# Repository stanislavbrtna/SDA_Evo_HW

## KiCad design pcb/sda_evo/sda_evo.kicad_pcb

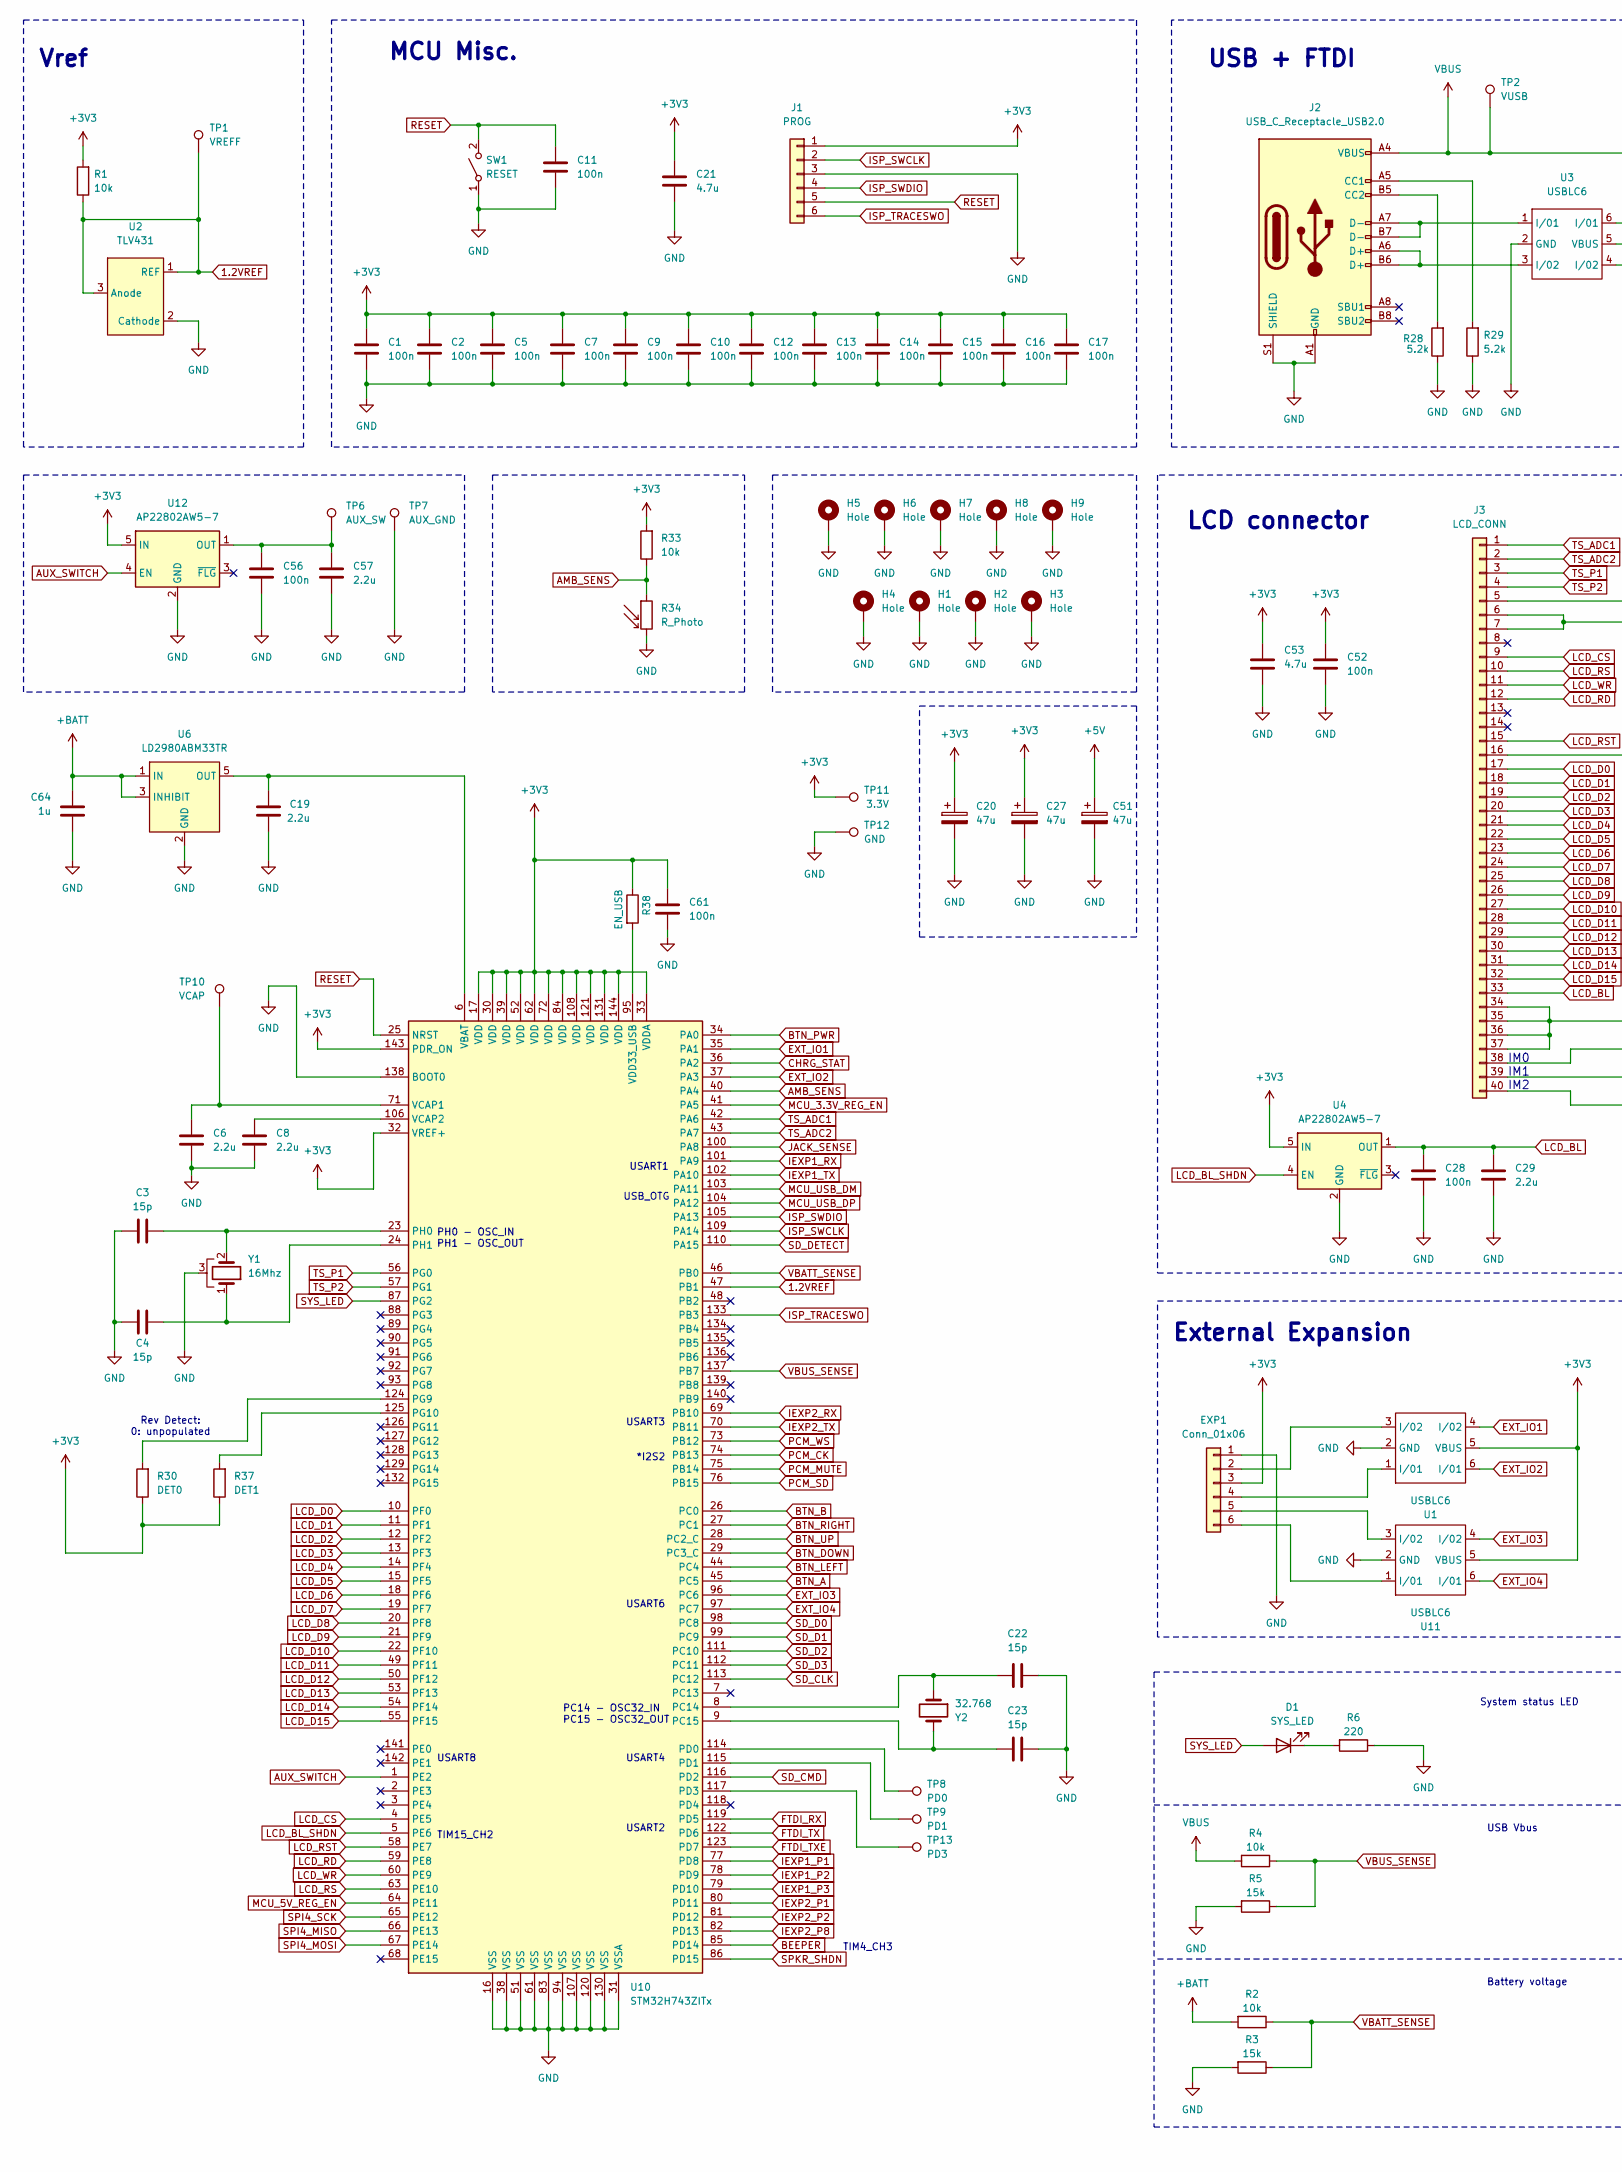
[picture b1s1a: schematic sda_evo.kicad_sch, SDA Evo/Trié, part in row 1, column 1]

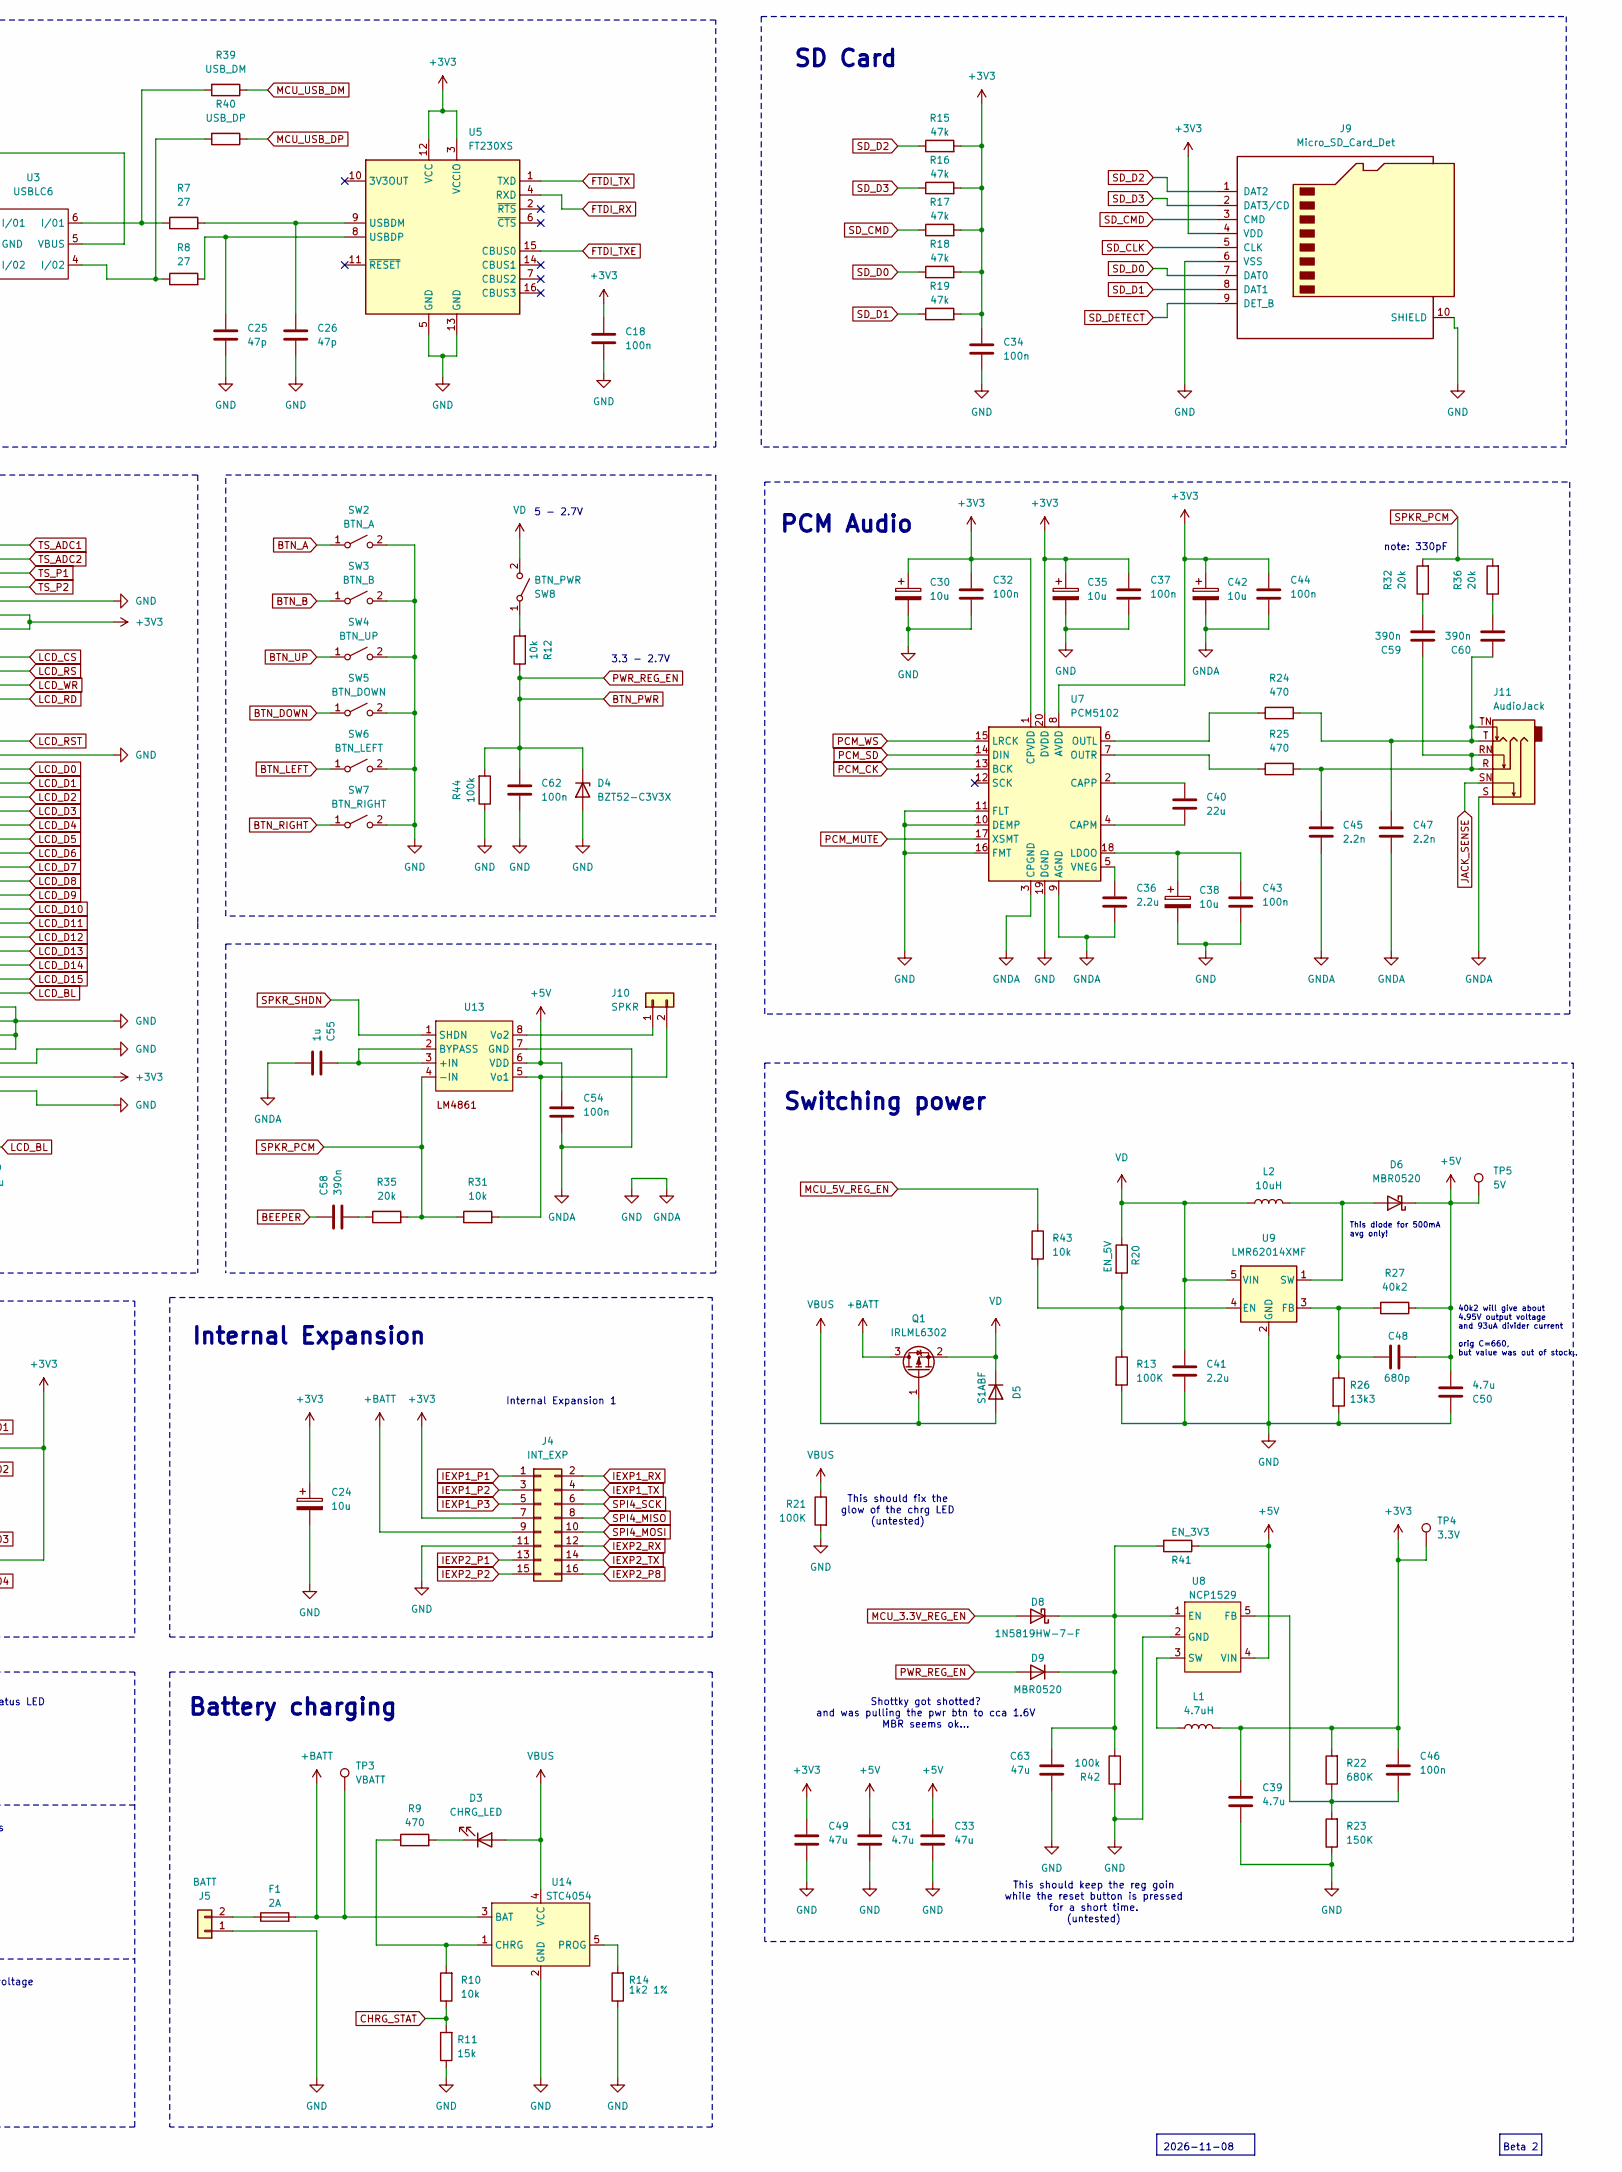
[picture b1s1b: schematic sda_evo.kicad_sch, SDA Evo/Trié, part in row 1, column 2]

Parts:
C1, C2, C5, C7, C9, C10, C11, C12, C13, C14, C15, C16, C17, C18, C28, C32, C34, C37, C43, C44, C46, C52, C54, C56, C61, C62: 100n; C_0805_2012Metric_Pad1.18x1.45mm_HandSolder
C3, C4, C22, C23: 15p; C_0805_2012Metric_Pad1.18x1.45mm_HandSolder
C6, C8, C19, C29, C36, C41, C57: 2.2u; C_0805_2012Metric_Pad1.18x1.45mm_HandSolder
C20, C27, C51: 47u; CP_EIA-7343-15_Kemet-W_Pad2.25x2.55mm_HandSolder
C21, C31, C39, C50, C53: 4.7u; C_0805_2012Metric_Pad1.18x1.45mm_HandSolder
C24, C30, C35, C38, C42: 10u; C_0805_2012Metric_Pad1.18x1.45mm_HandSolder
C25, C26: 47p; C_0805_2012Metric_Pad1.18x1.45mm_HandSolder
C33, C49, C63: 47u; C_0805_2012Metric_Pad1.18x1.45mm_HandSolder
C40: 22u; C_0805_2012Metric_Pad1.18x1.45mm_HandSolder
C45, C47: 2.2n; C_0805_2012Metric_Pad1.18x1.45mm_HandSolder
C48: 680p; C_0805_2012Metric_Pad1.18x1.45mm_HandSolder
C55, C64: 1u; C_0805_2012Metric_Pad1.18x1.45mm_HandSolder
C58, C59, C60: 390n; C_0805_2012Metric_Pad1.18x1.45mm_HandSolder
D1: SYS_LED; LED_D3.0mm_FlatTop
D3: CHRG_LED; LED_SMD_custom
D4: BZT52-C3V3X; Nexperia_CFP3_SOD-123W
D5: S1ABF; D_SMB
D6, D9: MBR0520; D_SOD-123
D8: 1N5819HW-7-F; D_SOD-123
EXP1: Conn_01x06; 2.54x6_flat
F1: 2A; Fuse_1206_3216Metric
H1, H2, H3, H4, H5, H6, H7, H8, H9: Hole; Hole 1,6mm
J1: PROG; PinHeader_1x06_P1.27mm_Vertical
J2: USB_C_Receptacle_USB2.0; USB_C
J3: LCD_CONN; Hirose_FH12-40S-0.5SH_1x40-1MP_P0.50mm_Horizontal
J4: INT_EXP; PinHeader_2x08_P1.27mm_Vertical_SMD
J5: BATT; PinHeader_1x02_P2.54mm_Horizontal
J9: Micro_SD_Card_Det; SD-Connector
J10: SPKR; PinHeader_1x02_P1.27mm_Vertical
J11: AudioJack; 3.5 Jack
L1: 4.7uH; HCM1A4020V2
L2: 10uH; SDN0530MT100
Q1: IRLML6302; SOT-23
R1, R2, R4, R10, R12, R31, R33, R43: 10k; R_0805_2012Metric_Pad1.20x1.40mm_HandSolder
R3, R5, R11: 15k; R_0805_2012Metric_Pad1.20x1.40mm_HandSolder
R6: 220; R_0805_2012Metric_Pad1.20x1.40mm_HandSolder
R7, R8: 27; R_0805_2012Metric_Pad1.20x1.40mm_HandSolder
R9, R24, R25: 470; R_0805_2012Metric_Pad1.20x1.40mm_HandSolder
R13, R21: 100K; R_0805_2012Metric_Pad1.20x1.40mm_HandSolder
R14: 1k2 1%; R_0805_2012Metric_Pad1.20x1.40mm_HandSolder
R15, R16, R17, R18, R19: 47k; R_0805_2012Metric_Pad1.20x1.40mm_HandSolder
R20: EN_5V; SolderJumper-2_P1.3mm_Open_TrianglePad1.0x1.5mm
R22: 680K; R_0805_2012Metric_Pad1.20x1.40mm_HandSolder
R23: 150K; R_0805_2012Metric_Pad1.20x1.40mm_HandSolder
R26: 13k3; R_0805_2012Metric_Pad1.20x1.40mm_HandSolder
R27: 40k2; R_0805_2012Metric_Pad1.20x1.40mm_HandSolder
R28, R29: 5.2k; R_0805_2012Metric_Pad1.20x1.40mm_HandSolder
R30: DET0; SolderJumper-2_P1.3mm_Open_TrianglePad1.0x1.5mm
R32, R35, R36: 20k; R_0805_2012Metric_Pad1.20x1.40mm_HandSolder
R34: R_Photo; LED_D5.0mm
R37: DET1; SolderJumper-2_P1.3mm_Open_TrianglePad1.0x1.5mm
R38: EN_USB; SolderJumper-2_P1.3mm_Open_TrianglePad1.0x1.5mm
R39: USB_DM; SolderJumper-2_P1.3mm_Open_TrianglePad1.0x1.5mm
R40: USB_DP; SolderJumper-2_P1.3mm_Open_TrianglePad1.0x1.5mm
R41: EN_3V3; SolderJumper-2_P1.3mm_Open_TrianglePad1.0x1.5mm
R42, R44: 100k; R_0805_2012Metric_Pad1.20x1.40mm_HandSolder
SW1: RESET; SW_SPST_RESET
SW2: BTN_A; SW_SPST_PTS645
SW3: BTN_B; SW_SPST_PTS645
SW4: BTN_UP; SW_SPST_PTS645
SW5: BTN_DOWN; SW_SPST_PTS645
SW6: BTN_LEFT; SW_SPST_PTS645
SW7: BTN_RIGHT; SW_SPST_PTS645
SW8: BTN_PWR; SW_Push_1P1T_NO_CK_KMR2_PWR
TP1: VREFF; TestPoint_Pad_D1.0mm
TP2: VUSB; TestPoint_Pad_D1.0mm
TP3: VBATT; TestPoint_Pad_D1.0mm
TP4: 3.3V; TestPoint_Pad_D1.0mm
TP5: 5V; TestPoint_Pad_D1.0mm
TP6: AUX_SW; TestPoint_Pad_D2.5mm
TP7: AUX_GND; TestPoint_Pad_D2.5mm
TP8: PD0; TestPoint_Pad_D2.5mm
TP9: PD1; TestPoint_Pad_D2.5mm
TP10: VCAP; TestPoint_Pad_D1.0mm
TP11: 3.3V; TestPoint_Pad_D2.5mm
TP12: GND; TestPoint_Pad_D2.5mm
TP13: PD3; TestPoint_Pad_D2.5mm
U1, U3, U11: USBLC6; SOT-23-6_Handsoldering
U2: TLV431; TSOT-23
U4, U12: AP22802AW5-7; SOT-23-5_HandSoldering
U5: FT230XS; SSOP-16_3.9x4.9mm_P0.635mm
U6: LD2980ABM33TR; SOT-23-5_HandSoldering
U7: PCM5102; TSSOP-20_4.4x6.5mm_P0.65mm
U8: NCP1529; SOT-23-5_HandSoldering
U9: LMR62014XMF; SOT-23-5_HandSoldering
U10: STM32H743ZITx; LQFP-144_20x20mm_P0.5mm
U13: LM4861; HSOP-8-1EP_3.9x4.9mm_P1.27mm_EP2.41x3.1mm
U14: STC4054; SOT-23-5_HandSoldering
Y1: 16Mhz; SMDXT224
Y2: 32.768; Crystal_SMD_6.7x1.5mm_HandSoldering

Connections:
1.2VREF: R1.1, TP1.1, U2.1 (REF), U2.3 (Anode), U10.47 (PB1)
+3V3: C1.1, C2.1, C5.1, C7.1, C9.1, C10.1, C12.1, C13.1, C14.1, C15.1, C16.1, C17.1, C18.1, C20.1, C21.1, C24.1, C27.1, C30.1, C32.1, C34.1, C35.1, C37.1, C39.1, C42.1, C44.1, C46.1, C49.1, C52.1, C53.1, C61.1, EXP1.3, J1.1, J3.6, J3.7, J3.39, J4.7, J9.4 (VDD), L1.2, R1.2, R15.2, R16.2, R17.2, R18.2, R19.2, R22.2, R30.1, R33.2, R37.1, R38.1, TP4.1, TP11.1, U1.5 (VBUS), U4.5 (IN), U5.3 (VCCIO), U5.12 (VCC), U7.1 (CPVDD), U7.8 (AVDD), U7.20 (DVDD), U10.17 (VDD), U10.30 (VDD), U10.32 (VREF+), U10.33 (VDDA), U10.39 (VDD), U10.52 (VDD), U10.62 (VDD), U10.72 (VDD), U10.84 (VDD), U10.108 (VDD), U10.121 (VDD), U10.131 (VDD), U10.143 (PDR_ON), U10.144 (VDD), U11.5 (VBUS), U12.5 (IN)
+5V: C31.1, C33.1, C48.2, C50.1, C51.1, C54.1, D6.1 (K), R27.1, R41.1, TP5.1, U8.4 (VIN), U13.6 (VDD)
+BATT: C64.1, F1.2, J4.9, Q1.3 (D), R2.2, TP3.1, U6.1 (IN), U6.3 (INHIBIT), U14.3 (BAT)
AMB_SENS: R33.1, R34.1, U10.40 (PA4)
AUX_SWITCH: U10.1 (PE2), U12.4 (EN)
BEEPER: C58.1, U10.85 (PD14)
BTN_A: SW2.1 (A), U10.45 (PC5)
BTN_B: SW3.1 (A), U10.26 (PC0)
BTN_DOWN: SW5.1 (A), U10.29 (PC3_C)
BTN_LEFT: SW6.1 (A), U10.44 (PC4)
BTN_PWR: C62.1, D4.1 (K), D9.2 (A), R12.1, R44.2, U10.34 (PA0)
BTN_RIGHT: SW7.1 (A), U10.27 (PC1)
BTN_UP: SW4.1 (A), U10.28 (PC2_C)
CHRG_STAT: R10.1, R11.2, U10.36 (PA2)
EXT_IO1: U1.4 (I/02), U10.35 (PA1)
EXT_IO2: U1.6 (I/01), U10.37 (PA3)
EXT_IO3: U10.96 (PC6), U11.4 (I/02)
EXT_IO4: U10.97 (PC7), U11.6 (I/01)
FTDI_RX: U5.4 (RXD), U10.119 (PD5)
FTDI_TX: U5.1 (TXD), U10.122 (PD6)
FTDI_TXE: U5.15 (CBUS0), U10.123 (PD7)
GND: C1.2, C2.2, C3.1, C4.1, C5.2, C6.2, C7.2, C8.2, C9.2, C10.2, C11.2, C12.2, C13.2, C14.2, C15.2, C16.2, C17.2, C18.2, C19.2, C20.2, C21.2, C22.1, C23.1, C24.2, C25.2, C26.2, C27.2, C28.2, C29.2, C30.2, C31.2, C32.2, C33.2, C34.2, C35.2, C36.2, C37.2, C38.2, C39.2, C41.2, C42.2, C43.2, C44.2, C45.2, C47.2, C49.2, C50.2, C51.2, C52.2, C53.2, C54.2, C55.2, C56.2, C57.2, C61.2, C62.2, C63.2, C64.2, D4.2 (A), EXP1.1, H1.1, H2.1, H3.1, H4.1, H5.1, H6.1, H7.1, H8.1, H9.1, J1.3, J2.A1 (GND), J2.A12 (GND), J2.B1 (GND), J2.B12 (GND), J2.S1 (SHIELD), J3.5, J3.16, J3.34, J3.35, J3.36, J3.37, J3.38, J3.40, J4.11, J5.1, J9.6 (VSS), J9.10 (SHIELD), J11.S, R3.2, R5.2, R6.1, R11.1, R13.2, R14.1, R21.2, R23.1, R26.2, R28.1, R29.1, R34.2, R42.2, R44.1, SW1.1 (A), SW2.2 (B), SW3.2 (B), SW4.2 (B), SW5.2 (B), SW6.2 (B), SW7.2 (B), TP7.1, TP12.1, U1.2 (GND), U2.2 (Cathode), U3.2 (GND), U4.2 (GND), U5.5 (GND), U5.13 (GND), U6.2 (GND), U7.3 (CPGND), U7.9 (AGND), U7.10 (DEMP), U7.11 (FLT), U7.16 (FMT), U7.19 (DGND), U8.2 (GND), U9.2 (GND), U10.16 (VSS), U10.31 (VSSA), U10.38 (VSS), U10.51 (VSS), U10.61 (VSS), U10.83 (VSS), U10.94 (VSS), U10.107 (VSS), U10.120 (VSS), U10.130 (VSS), U10.138 (BOOT0), U11.2 (GND), U12.2 (GND), U13.7 (GND), U14.2 (GND), Y1.3
IEXP1_P1: J4.1, U10.77 (PD8)
IEXP1_P2: J4.3, U10.78 (PD9)
IEXP1_P3: J4.5, U10.79 (PD10)
IEXP1_RX: J4.2, U10.101 (PA9)
IEXP1_TX: J4.4, U10.102 (PA10)
IEXP2_P1: J4.13, U10.80 (PD11)
IEXP2_P2: J4.15, U10.81 (PD12)
IEXP2_P8: J4.16, U10.82 (PD13)
IEXP2_RX: J4.12, U10.69 (PB10)
IEXP2_TX: J4.14, U10.70 (PB11)
ISP_SWCLK: J1.2, U10.109 (PA14)
ISP_SWDIO: J1.4, U10.105 (PA13)
ISP_TRACESWO: J1.6, U10.133 (PB3)
JACK_SENSE: J11.SN, U10.100 (PA8)
LCD_BL: C28.1, C29.1, J3.33, U4.1 (OUT)
LCD_BL_SHDN: U4.4 (EN), U10.5 (PE6)
LCD_CS: J3.9, U10.4 (PE5)
LCD_D0: J3.17, U10.10 (PF0)
LCD_D1: J3.18, U10.11 (PF1)
LCD_D2: J3.19, U10.12 (PF2)
LCD_D3: J3.20, U10.13 (PF3)
LCD_D4: J3.21, U10.14 (PF4)
LCD_D5: J3.22, U10.15 (PF5)
LCD_D6: J3.23, U10.18 (PF6)
LCD_D7: J3.24, U10.19 (PF7)
LCD_D8: J3.25, U10.20 (PF8)
LCD_D9: J3.26, U10.21 (PF9)
LCD_D10: J3.27, U10.22 (PF10)
LCD_D11: J3.28, U10.49 (PF11)
LCD_D12: J3.29, U10.50 (PF12)
LCD_D13: J3.30, U10.53 (PF13)
LCD_D14: J3.31, U10.54 (PF14)
LCD_D15: J3.32, U10.55 (PF15)
LCD_RD: J3.12, U10.59 (PE8)
LCD_RS: J3.10, U10.63 (PE10)
LCD_RST: J3.15, U10.58 (PE7)
LCD_WR: J3.11, U10.60 (PE9)
MCU_3.3V_REG_EN: D8.2 (A), U10.41 (PA5)
MCU_5V_REG_EN: R43.1, U10.64 (PE11)
MCU_USB_DM: R39.1, U10.103 (PA11)
MCU_USB_DP: R40.1, U10.104 (PA12)
unnamed: C45.1, C59.1, J11.R, J11.RN, R25.2
unnamed: C47.1, C60.1, J11.T, J11.TN, R24.2
unnamed: C58.2, R35.1
unnamed: C59.2, R32.1
unnamed: C60.2, R36.1
unnamed: D1.1 (K), R6.2
unnamed: D3.1 (K), R9.2
unnamed: D6.2 (A), L2.2, U9.1 (SW)
unnamed: C63.1, D8.1 (K), D9.1 (K), R41.2, R42.1, U8.1 (EN)
unnamed: EXP1.2, U1.3 (I/02)
unnamed: EXP1.4, U1.1 (I/01)
unnamed: EXP1.5, U11.3 (I/02)
unnamed: EXP1.6, U11.1 (I/01)
unnamed: J2.A5 (CC1), R29.2
unnamed: J2.B5 (CC2), R28.2
unnamed: J2.A6 (D+), J2.B6 (D+), U3.3 (I/02)
unnamed: J2.A7 (D-), J2.B7 (D-), U3.1 (I/01)
unnamed: F1.1, J5.2
unnamed: J10.1, U13.8 (Vo2)
unnamed: J10.2, R31.2, U13.5 (Vo1)
unnamed: R7.1, R39.2, U3.6 (I/01)
unnamed: R8.1, R40.2, U3.4 (I/02)
unnamed: R12.2, SW8.1 (A)
unnamed: C26.1, R7.2, U5.9 (USBDM)
unnamed: C25.1, R8.2, U5.8 (USBDP)
unnamed: C40.2, U7.4 (CAPM)
unnamed: C40.1, U7.2 (CAPP)
unnamed: C38.1, C43.1, U7.18 (LDOO)
unnamed: R24.1, U7.6 (OUTL)
unnamed: R25.1, U7.7 (OUTR)
unnamed: C36.1, U7.5 (VNEG)
unnamed: C46.2, R22.1, R23.2, U8.5 (FB)
unnamed: L1.1, U8.3 (SW)
unnamed: R13.1, R20.2, R43.2, U9.4 (EN)
unnamed: C48.1, R26.1, R27.2, U9.3 (FB)
unnamed: C22.2, U10.8 (PC14), Y2.1
unnamed: C23.2, U10.9 (PC15), Y2.2
unnamed: TP8.1, U10.114 (PD0)
unnamed: TP9.1, U10.115 (PD1)
unnamed: TP13.1, U10.117 (PD3)
unnamed: R30.2, U10.124 (PG9)
unnamed: R37.2, U10.125 (PG10)
unnamed: C3.2, U10.23 (PH0), Y1.2
unnamed: C4.2, U10.24 (PH1), Y1.1
unnamed: C19.1, U6.5 (OUT), U10.6 (VBAT)
unnamed: C6.1, TP10.1, U10.71 (VCAP1)
unnamed: C8.1, U10.106 (VCAP2)
unnamed: R38.2, U10.95 (VDD33_USB)
unnamed: C56.1, C57.1, TP6.1, U12.1 (OUT)
unnamed: C55.1, U13.2 (BYPASS), U13.3 (+IN)
unnamed: R9.1, R10.2, U14.1 (CHRG)
unnamed: R14.2, U14.5 (PROG)
PCM_CK: U7.13 (BCK), U10.74 (PB13)
PCM_MUTE: U7.17 (XSMT), U10.75 (PB14)
PCM_SD: U7.14 (DIN), U10.76 (PB15)
PCM_WS: U7.15 (LRCK), U10.73 (PB12)
RESET: C11.1, J1.5, SW1.2 (B), U10.25 (NRST)
SD_CLK: J9.5 (CLK), U10.113 (PC12)
SD_CMD: J9.3 (CMD), R17.1, U10.116 (PD2)
SD_D0: J9.7 (DAT0), R18.1, U10.98 (PC8)
SD_D1: J9.8 (DAT1), R19.1, U10.99 (PC9)
SD_D2: J9.1 (DAT2), R15.1, U10.111 (PC10)
SD_D3: J9.2 (DAT3/CD), R16.1, U10.112 (PC11)
SD_DETECT: J9.9 (DET_B), U10.110 (PA15)
SPI4_MISO: J4.8, U10.66 (PE13)
SPI4_MOSI: J4.10, U10.67 (PE14)
SPI4_SCK: J4.6, U10.65 (PE12)
SPKR_PCM: R31.1, R32.2, R35.2, R36.2, U13.4 (-IN)
SPKR_SHDN: U10.86 (PD15), U13.1 (SHDN)
SYS_LED: D1.2 (A), U10.87 (PG2)
TS_ADC1: J3.1, U10.42 (PA6)
TS_ADC2: J3.2, U10.43 (PA7)
TS_P1: J3.3, U10.56 (PG0)
TS_P2: J3.4, U10.57 (PG1)
VBATT_SENSE: R2.1, R3.1, U10.46 (PB0)
VBUS: D3.2 (A), D5.2 (A), J2.A4 (VBUS), J2.A9 (VBUS), J2.B4 (VBUS), J2.B9 (VBUS), Q1.1 (G), R4.2, R21.1, TP2.1, U3.5 (VBUS), U14.4 (VCC)
VBUS_SENSE: R4.1, R5.1, U10.137 (PB7)
VD: C41.1, D5.1 (K), L2.1, Q1.2 (S), R20.1, SW8.2 (B), U9.5 (VIN)

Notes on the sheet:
MCU Misc.
Battery voltage
USART1
*I2S2
Internal Expansion 1
Beta 2
40k2 will give about 4.95V output voltage and 93uA divider current orig C=660, but value was out of stock..
Internal Expansion
3.3 - 2.7V
USART2
IM0 IM1 IM2
USB + FTDI
SD Card
System status LED
USART3
PCM Audio
USART8
USART4
5 - 2.7V
Vref
This should fix the glow of the chrg LED (untested)
PH0 - OSC_IN PH1 - OSC_OUT
Switching power
Rev Detect: 0: unpopulated
note: 330pF
2026-11-08
LCD connector
This diode for 500mA avg only!
USART6
Shottky got shotted? and was pulling the pwr btn to cca 1.6V MBR seems ok...
External Expansion
TIM4_CH3
TIM15_CH2
USB Vbus
PC14 - OSC32_IN PC15 - OSC32_OUT
USB_OTG
This should keep the reg goin while the reset button is pressed for a short time. (untested)
Battery charging

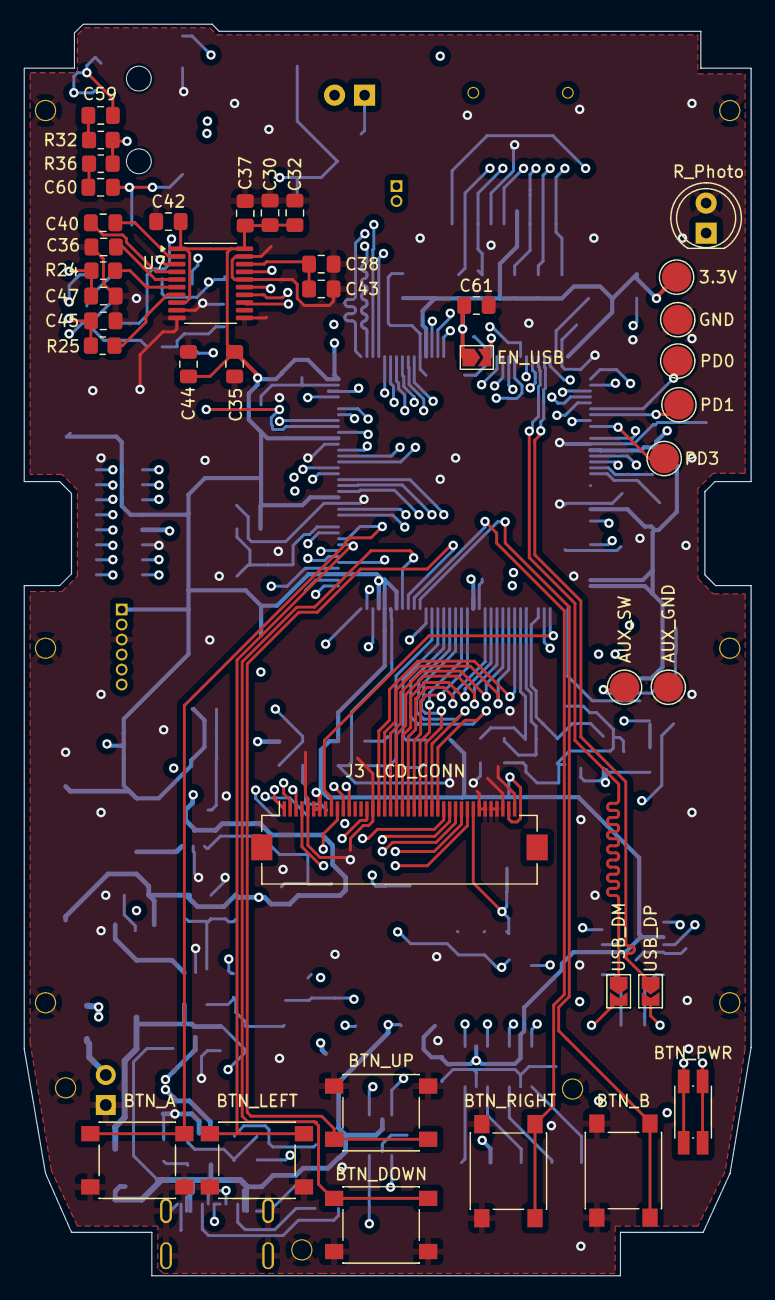
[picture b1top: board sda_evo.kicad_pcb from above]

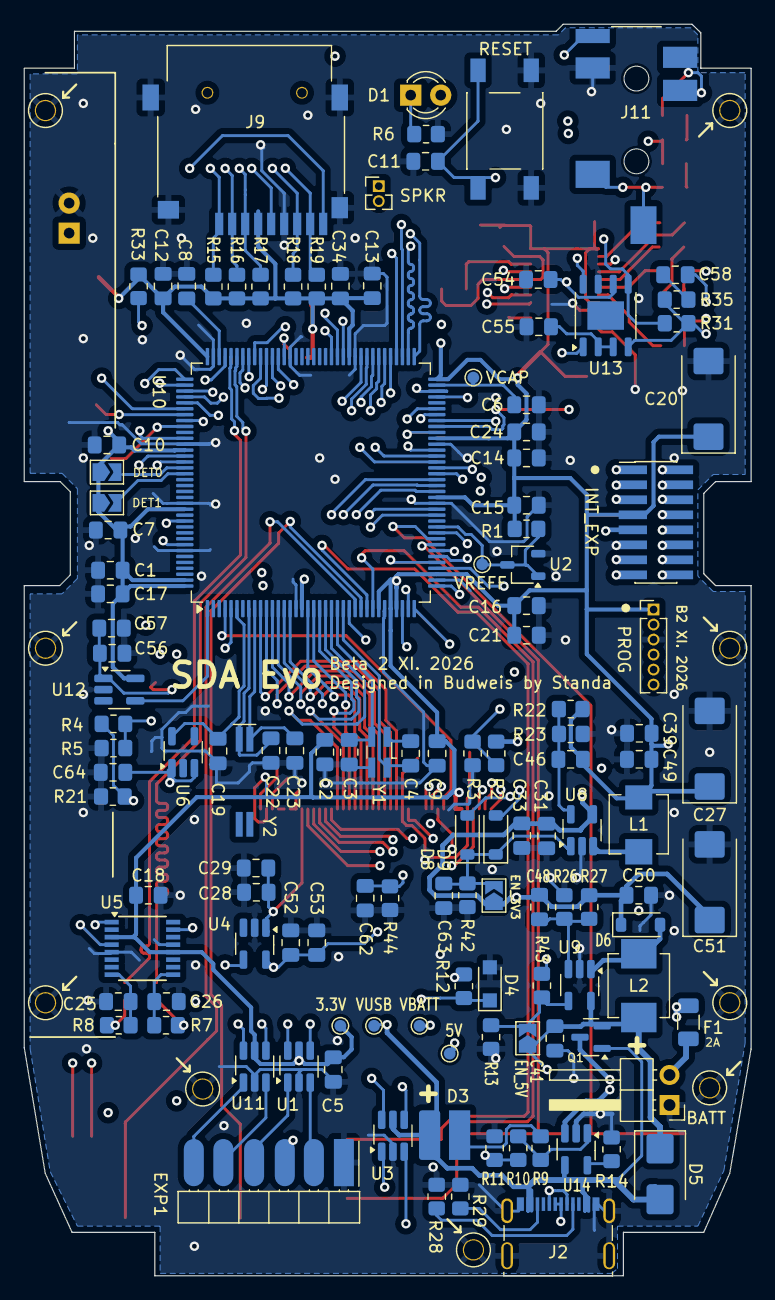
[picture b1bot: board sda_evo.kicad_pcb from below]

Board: 4 copper layers, 61.5 x 105.9 mm, 174 parts (135 on the bottom side), 142 nets.

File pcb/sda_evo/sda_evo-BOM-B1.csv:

"Reference","Value","Datasheet","Footprint","Qty","DNP"
"C1,C2,C5,C7,C9,C10,C11,C12,C13,C14,C15,C16,C17,C18,C28,C32,C34,C37,C43,C44,C46,C52,C54,C56","100n","~","Capacitor_SMD:C_0805_2012Metric_Pad1.18x1.45mm_HandSolder","24",""
"C3,C4,C22,C23","15p","~","Capacitor_SMD:C_0805_2012Metric_Pad1.18x1.45mm_HandSolder","4",""
"C6,C8,C19,C29,C36,C41,C57","2.2u","~","Capacitor_SMD:C_0805_2012Metric_Pad1.18x1.45mm_HandSolder","7",""
"C20,C27,C33,C49,C51","47u","~","Capacitor_SMD:C_0805_2012Metric_Pad1.18x1.45mm_HandSolder,Capacitor_Tantalum_SMD:CP_EIA-7343-15_Kemet-W_Pad2.25x2.55mm_HandSolder","5",""
"C21,C31,C39,C50,C53","4.7u","~","Capacitor_SMD:C_0805_2012Metric_Pad1.18x1.45mm_HandSolder","5",""
"C24,C30,C35,C38,C42","10u","~","Capacitor_SMD:C_0805_2012Metric_Pad1.18x1.45mm_HandSolder","5",""
"C25,C26","47p","~","Capacitor_SMD:C_0805_2012Metric_Pad1.18x1.45mm_HandSolder","2",""
"C40","22u","~","Capacitor_SMD:C_0805_2012Metric_Pad1.18x1.45mm_HandSolder","1",""
"C45,C47","2.2n","~","Capacitor_SMD:C_0805_2012Metric_Pad1.18x1.45mm_HandSolder","2",""
"C48","680p","~","Capacitor_SMD:C_0805_2012Metric_Pad1.18x1.45mm_HandSolder","1",""
"C55","1u","~","Capacitor_SMD:C_0805_2012Metric_Pad1.18x1.45mm_HandSolder","1",""
"C58,C59,C60","390n","~","Capacitor_SMD:C_0805_2012Metric_Pad1.18x1.45mm_HandSolder","3",""
"D1","SYS_LED","~","LED_THT:LED_D3.0mm_FlatTop","1",""
"D3","CHRG_LED","~","sda-parts:LED_SMD_custom","1",""
"D4","BZT52-C3V3X","~","Diode_SMD:Nexperia_CFP3_SOD-123W","1",""
"D5","S1ABF","https://www.vishay.com/docs/85748/1n4148w.pdf","Diode_SMD:D_SMB","1",""
"D6","MBR0520","http://www.mccsemi.com/up_pdf/MBR0520~MBR0580(SOD123).pdf","Diode_SMD:D_SOD-123","1",""
"D7,D8,D9","1N5819HW-7-F","~","Diode_SMD:D_SOD-123","3",""
"EXP1","Conn_01x06","~","sda-parts:2.54x6_flat","1",""
"F1","2A","~","Fuse:Fuse_1206_3216Metric","1",""
"H1,H2,H3,H4,H5,H6,H7,H8,H9","Hole","~","sda-parts:Hole 1,6mm","9",""
"J1","PROG","~","Connector_PinHeader_1.27mm:PinHeader_1x06_P1.27mm_Vertical","1",""
"J2","USB_C_Receptacle_USB2.0","https://www.usb.org/sites/default/files/documents/usb_type-c.zip","sda-parts:USB_C","1",""
"J3","LCD_CONN","~","Connector_FFC-FPC:Hirose_FH12-40S-0.5SH_1x40-1MP_P0.50mm_Horizontal","1",""
"J4","INT_EXP","~","Connector_PinHeader_1.27mm:PinHeader_2x08_P1.27mm_Vertical_SMD","1",""
"J5","BATT","~","Connector_PinHeader_2.54mm:PinHeader_1x02_P2.54mm_Horizontal","1",""
"J9","Micro_SD_Card_Det","https://www.hirose.com/product/en/download_file/key_name/DM3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","sda-parts:SD-Connector","1",""
"J10","SPKR","~","Connector_PinHeader_1.27mm:PinHeader_1x02_P1.27mm_Vertical","1",""
"J11","AudioJack","~","sda-parts:3.5 Jack","1",""
"L1","4.7uH","~","sda-parts:HCM1A4020V2","1",""
"L2","10uH","~","sda-parts:SDN0530MT100","1",""
"Q1","IRLML6302","https://www.infineon.com/dgdl/irlml5203pbf.pdf?fileId=5546d4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","Package_TO_SOT_SMD:SOT-23","1",""
"R1,R2,R4,R10,R12,R31,R33","10k","~","Resistor_SMD:R_0805_2012Metric_Pad1.20x1.40mm_HandSolder","7",""
"R3,R5,R11","15k","~","Resistor_SMD:R_0805_2012Metric_Pad1.20x1.40mm_HandSolder","3",""
"R6","220","~","Resistor_SMD:R_0805_2012Metric_Pad1.20x1.40mm_HandSolder","1",""
"R7,R8","27","~","Resistor_SMD:R_0805_2012Metric_Pad1.20x1.40mm_HandSolder","2",""
"R9,R24,R25","470","~","Resistor_SMD:R_0805_2012Metric_Pad1.20x1.40mm_HandSolder","3",""
"R13","100K","~","Resistor_SMD:R_0805_2012Metric_Pad1.20x1.40mm_HandSolder","1",""
"R14","1k2 1%","~","Resistor_SMD:R_0805_2012Metric_Pad1.20x1.40mm_HandSolder","1",""
"R15,R16,R17,R18,R19,R21","47k","~","Resistor_SMD:R_0805_2012Metric_Pad1.20x1.40mm_HandSolder","6",""
"R20,R41","placeholder","~","Resistor_SMD:R_0805_2012Metric_Pad1.20x1.40mm_HandSolder","2",""
"R22","680K","~","Resistor_SMD:R_0805_2012Metric_Pad1.20x1.40mm_HandSolder","1",""
"R23","150K","~","Resistor_SMD:R_0805_2012Metric_Pad1.20x1.40mm_HandSolder","1",""
"R26","13k3","~","Resistor_SMD:R_0805_2012Metric_Pad1.20x1.40mm_HandSolder","1",""
"R27","40k2","~","Resistor_SMD:R_0805_2012Metric_Pad1.20x1.40mm_HandSolder","1",""
"R28,R29","5.2k","~","Resistor_SMD:R_0805_2012Metric_Pad1.20x1.40mm_HandSolder","2",""
"R30,R37","0","~","Resistor_SMD:R_0805_2012Metric_Pad1.20x1.40mm_HandSolder","2",""
"R32,R35,R36","20k","~","Resistor_SMD:R_0805_2012Metric_Pad1.20x1.40mm_HandSolder","3",""
"R34","R_Photo","~","LED_THT:LED_D5.0mm","1",""
"R42,R43","10K","~","Resistor_SMD:R_0805_2012Metric_Pad1.20x1.40mm_HandSolder","2",""
"SW1","RESET","~","sda-parts:SW_SPST_RESET","1",""
"SW2","BTN_A","~","Button_Switch_SMD:SW_SPST_PTS645","1",""
"SW3","BTN_B","~","Button_Switch_SMD:SW_SPST_PTS645","1",""
"SW4","BTN_UP","~","Button_Switch_SMD:SW_SPST_PTS645","1",""
"SW5","BTN_DOWN","~","Button_Switch_SMD:SW_SPST_PTS645","1",""
"SW6","BTN_LEFT","~","Button_Switch_SMD:SW_SPST_PTS645","1",""
"SW7","BTN_RIGHT","~","Button_Switch_SMD:SW_SPST_PTS645","1",""
"SW8","BTN_PWR","~","sda-parts:SW_Push_1P1T_NO_CK_KMR2_PWR","1",""
"TP1","VREFF","~","TestPoint:TestPoint_Pad_D1.0mm","1",""
"TP2","VUSB","~","TestPoint:TestPoint_Pad_D1.0mm","1",""
"TP3","VBATT","~","TestPoint:TestPoint_Pad_D1.0mm","1",""
"TP4,TP11","3.3V","~","TestPoint:TestPoint_Pad_D1.0mm,TestPoint:TestPoint_Pad_D2.5mm","2",""
"TP5","5V","~","TestPoint:TestPoint_Pad_D1.0mm","1",""
"TP6","AUX_SW","~","TestPoint:TestPoint_Pad_D2.5mm","1",""
"TP7","AUX_GND","~","TestPoint:TestPoint_Pad_D2.5mm","1",""
"TP8","PD3","~","TestPoint:TestPoint_Pad_D2.5mm","1",""
"TP9","PD4","~","TestPoint:TestPoint_Pad_D2.5mm","1",""
"TP10","VCAP","~","TestPoint:TestPoint_Pad_D1.0mm","1",""
"TP12","GND","~","TestPoint:TestPoint_Pad_D2.5mm","1",""
"U1,U3,U11","USBLC6","","Package_TO_SOT_SMD:TSOT-23-6_HandSoldering","3",""
"U2","TLV431","","Package_TO_SOT_SMD:TSOT-23","1",""
"U4,U12","AP22802AW5-7","https://www.diodes.com/assets/Datasheets/AP22804_14.pdf","Package_TO_SOT_SMD:SOT-23-5_HandSoldering","2",""
"U5","FT230XS","https://www.ftdichip.com/Support/Documents/DataSheets/ICs/DS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","Package_SO:SSOP-16_3.9x4.9mm_P0.635mm","1",""
"U7","PCM5102","http://www.ti.com/lit/ds/symlink/pcm5102.pdf","Package_SO:TSSOP-20_4.4x6.5mm_P0.65mm","1",""
"U8","NCP1529","","Package_TO_SOT_SMD:SOT-23-5_HandSoldering","1",""
"U9","LMR62014XMF","http://www.ti.com/lit/ds/symlink/lmr62014.pdf","Package_TO_SOT_SMD:SOT-23-5_HandSoldering","1",""
"U10","STM32H743ZITx","http://www.st.com/st-web-ui/static/active/en/resource/techni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","Package_QFP:LQFP-144_20x20mm_P0.5mm","1",""
"U13","LM4861","","Package_SO:HSOP-8-1EP_3.9x4.9mm_P1.27mm_EP2.41x3.1mm","1",""
"U14","STC4054","","Package_TO_SOT_SMD:SOT-23-5_HandSoldering","1",""
"Y1","16Mhz","~","sda-parts:SMDXT224","1",""
"Y2","32.768","~","sda-parts:Crystal_SMD_6.7x1.5mm_HandSoldering","1",""

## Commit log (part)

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2024-03-28 Adaded part mockups. PCB is nearly finished.
2024-03-29 i2s vias lenght matched
2024-03-29 3.5 jack moved a bit, added few holes to the casing
2024-05-03 PCB: footprints adjusted
2025-06-20 did some stuff
2025-06-20 pcb: dac turned around
2025-12-08 misc updates, file cleanup
2025-12-08 repo cleanup, board twaked
2025-12-08 conn door added
2025-12-08 cap moved out of te way
2025-12-16 case cleanup, port cover finalized
2025-12-16 datasheets cleanup, pcb finalized
2025-12-18 Fab layers cleaned up
2026-04-18 commit before beta1
2026-04-22 chore: migrated to freecad 1.1
2026-04-22 feat: fixed b0 problems, pushed to b1
2026-05-25 PCB updates for B1
2026-05-25 PCB and case files updated
